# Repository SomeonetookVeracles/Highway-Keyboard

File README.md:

I'm building a minimalistic keyboard, something simple and stripped down. It's my first time working on a large PCB, and I kept getting distracted by feature creep and add-ons. So I'm going back to basics. I want this to be a barebones board that helps me sharpen my skills and really dial in the core of what makes a great keyboard.

I learned a lot while doing this, and explored concepts like impedence matching and zones, something that I've done before but never really had to prioritize.

If I do this again, I'm using a ESP-32 chip, making a CPU clock with decoupling capacitors was exhausting and annoyed me to no small extent lmao.

# Bill of Materials

| Reference | Qty | Value | Footprint | Description | DigiKey Link | Amazon Link | Unit Price | Total Price |
|-----------|-----|-------|-----------|-------------|--------------|-------------|------------|-------------|
| **Capacitors** | | | | | | | | |
| C1 | 1 | 1uF | 0603 | Ceramic Capacitor | [YAGEO CC0603ZRY5V7BB105](https://www.digikey.com/en/products/detail/yageo/CC0603ZRY5V7BB105/2103110) | [0603 Capacitor Kit](https://www.amazon.com/100pcs-Multilayer-Ceramic-Capacitor-0-5pF/dp/B0DDC637G1) | $0.03 | $0.03 |
| C2,C3,C4 | 3 | 0.1uF | 0603 | Ceramic Capacitor | [KEMET C0603C104J4RAC7867](https://www.digikey.com/en/products/detail/kemet/C0603C104J4RAC7867/411096) | [0603 Capacitor Kit](https://www.amazon.com/100pcs-Multilayer-Ceramic-Capacitor-0-5pF/dp/B0DDC637G1) | $0.02 | $0.06 |
| C5 | 1 | 10uF | 0603 | Ceramic Capacitor | [YAGEO CC0603KRX5R6BB106](https://www.digikey.com/en/products/detail/yageo/CC0603KRX5R6BB106/5195191) | [0603 Capacitor Kit](https://www.amazon.com/100pcs-Multilayer-Ceramic-Capacitor-0-5pF/dp/B0DDC637G1) | $0.08 | $0.08 |
| C6,C7 | 2 | 22pF | 0603 | Ceramic Capacitor | [DigiKey 0603 Capacitors](https://www.digikey.com/en/products/filter/ceramic-capacitors/60) | [0603 Capacitor Kit](https://www.amazon.com/100pcs-Multilayer-Ceramic-Capacitor-0-5pF/dp/B0DDC637G1) | $0.02 | $0.04 |
| **Diodes** | | | | | | | | |
| D1-D87 | 87 | D_Small | 0603 | Small Signal Diode | [DigiKey 0603 Diodes](https://www.digikey.com/en/products/filter/diodes-rectifiers-single/280) | [SMD Component Kit](https://www.amazon.com/Component-Assortment-Capacitor-Transistor-Soldering/dp/B07GMRJC1Q) | $0.05 | $4.35 |
| **Fuse** | | | | | | | | |
| F1 | 1 | 500mA | 1812 | PTC Resettable Fuse | [Bourns MF-MSMF050-2](https://www.digikey.com/en/products/detail/bourns-inc/MF-MSMF050-2/662832) | [Fuse Kit](https://www.amazon.com/s?k=500mA+PTC+fuse) | $0.32 | $0.32 |
| **Connectors** | | | | | | | | |
| J1 | 1 | USB_C_Receptacle | HRO TYPE-C-31-M-12 | USB-C 2.0 Connector | [JAE DX07S016JA3R1500](https://www.digikey.com/en/products/detail/jae-electronics/DX07S016JA3R1500/5978550) | [USB-C Connector](https://www.amazon.com/s?k=TYPE-C-31-M-12) | $0.38 | $0.38 |
| **Resistors** | | | | | | | | |
| R1,R4 | 2 | 10k | 0603 | Chip Resistor | [YAGEO RC0603JR-0710KL](https://www.digikey.com/en/products/detail/yageo/RC0603JR-0710KL/726700) | [0603 Resistor Kit](https://www.amazon.com/s?k=0603+resistor+kit) | $0.01 | $0.02 |
| R2,R3 | 2 | 22Ω | 0603 | Chip Resistor | [DigiKey 0603 Resistors](https://www.digikey.com/en/products/filter/resistors/chip-resistor-surface-mount/0603/52) | [0603 Resistor Kit](https://www.amazon.com/s?k=0603+resistor+kit) | $0.01 | $0.02 |
| R5 | 1 | 1M | 0603 | Chip Resistor | [DigiKey 0603 Resistors](https://www.digikey.com/en/products/filter/resistors/chip-resistor-surface-mount/0603/52) | [0603 Resistor Kit](https://www.amazon.com/s?k=0603+resistor+kit) | $0.01 | $0.01 |
| R6,R7 | 2 | 5.11k | 0603 | Chip Resistor | [DigiKey 0603 Resistors](https://www.digikey.com/en/products/filter/resistors/chip-resistor-surface-mount/0603/52) | [0603 Resistor Kit](https://www.amazon.com/s?k=0603+resistor+kit) | $0.01 | $0.02 |
| **Switches** | | | | | | | | |
| SW1-SW87 | 87 | SW_Push_45deg | Cherry MX Compatible | Mechanical Key Switch | [Cherry MX1A-E1NW](https://www.digikey.com/en/products/detail/cherry-americas-llc/MX1A-E1NW/20180) | [Cherry MX Switches](https://www.amazon.com/s?k=cherry+mx+switches) | $1.25 | $108.75 |
| SWRST1 | 1 | SW_PUSH | SMD Tactile | Reset Switch | [DigiKey Tactile Switches](https://www.digikey.com/en/products/filter/tactile-switches/197) | [Tactile Switch Kit](https://www.amazon.com/s?k=SMD+tactile+switch) | $0.15 | $0.15 |
| **Microcontroller** | | | | | | | | |
| U1 | 1 | ATmega32U4-A | TQFP-44 | 8-bit Microcontroller | [ATMEGA32U4-AU](https://www.digikey.com/en/products/detail/microchip-technology/ATMEGA32U4-AU/1914602) | [ATmega32U4 Module](https://www.amazon.com/s?k=atmega32u4) | $5.39 | $5.39 |
| **Crystal** | | | | | | | | |
| Y1 | 1 | 16MHz | 0603-4Pin | Crystal Oscillator | [TXC 7V-16.000MAAE-T](https://www.digikey.com/en/products/detail/txc-corporation/7V-16-000MAAE-T/2626978) | [16MHz Crystal](https://www.amazon.com/s?k=16MHz+crystal+SMD) | $0.35 | $0.35 |

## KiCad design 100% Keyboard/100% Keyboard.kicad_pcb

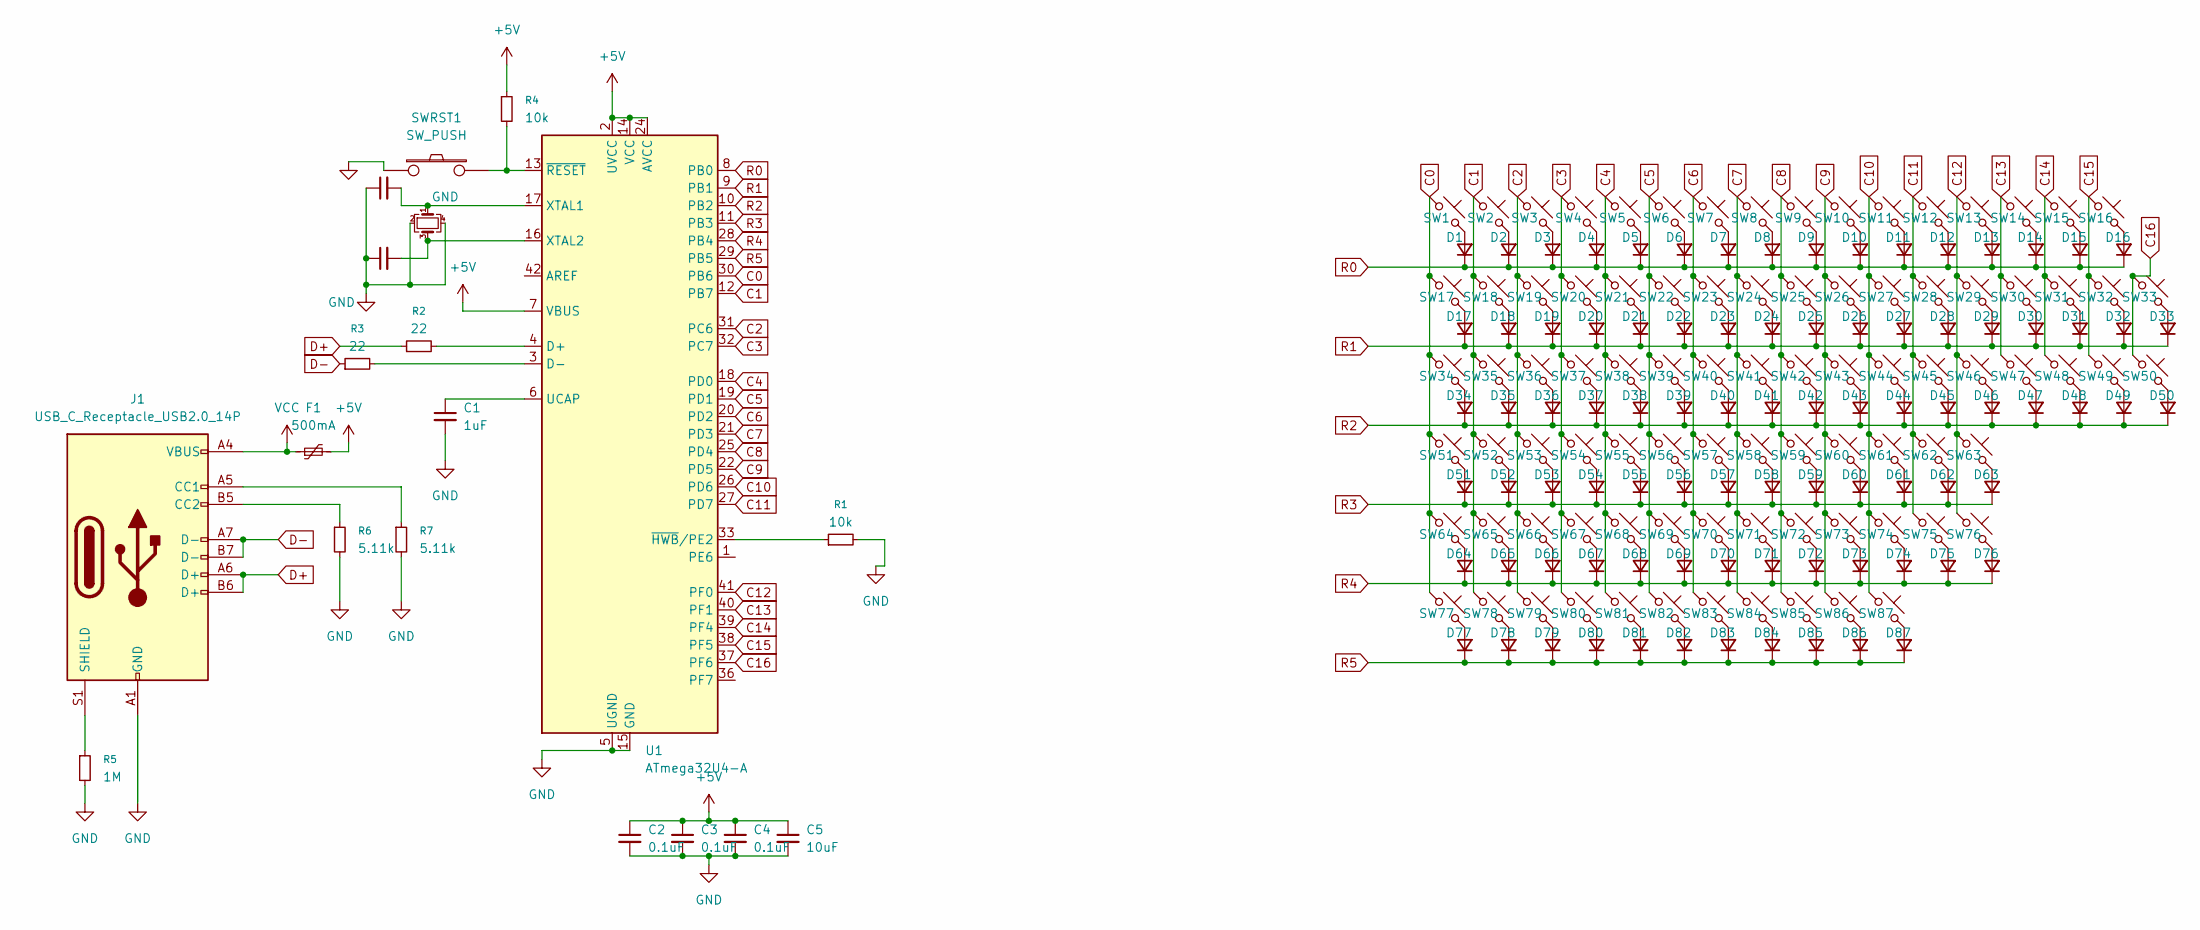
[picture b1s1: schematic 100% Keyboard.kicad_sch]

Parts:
C1: 1uF; C_0201_0603Metric_Pad0.64x0.40mm_HandSolder
C2, C3, C4: 0.1uF; C_0201_0603Metric_Pad0.64x0.40mm_HandSolder
C5: 10uF; C_0201_0603Metric_Pad0.64x0.40mm_HandSolder
C6, C7: 22pF; C_0201_0603Metric_Pad0.64x0.40mm_HandSolder
D1, D2, D3, D4, D5, D6, D7, D8, D9, D10, D11, D12, D13, D14, D15, D16, D17, D18, D19, D20, D21, D22, D23, D24, D25, D26, D27, D28, D29, D30, D31, D32, D33, D34, D35, D36, D37, D38, D39, D40, D41, D42, D43, D44, D45, D46, D47, D48, D49, D50, D51, D52, D53, D54, D55, D56, D57, D58, D59, D60, D61, D62, D63, D64, D65, D66, D67, D68, D69, D70, D71, D72, D73, D74, D75, D76, D77, D78, D79, D80, D81, D82, D83, D84, D85, D86, D87: D_Small; D_0603_1608Metric_Pad1.05x0.95mm_HandSolder
F1: 500mA; Fuse_Bourns_MF-RG500
J1: USB_C_Receptacle_USB2.0_14P; USB_C_Receptacle_HRO_TYPE-C-31-M-12
R1, R4: 10k; R_0201_0603Metric_Pad0.64x0.40mm_HandSolder
R2, R3: 22; R_0201_0603Metric_Pad0.64x0.40mm_HandSolder
R5: 1M; R_0201_0603Metric_Pad0.64x0.40mm_HandSolder
R6, R7: 5.11k; R_0201_0603Metric_Pad0.64x0.40mm_HandSolder
SW1, SW2, SW3, SW4, SW5, SW6, SW7, SW8, SW9, SW10, SW11, SW12, SW13, SW14, SW15, SW16, SW17, SW18, SW19, SW20, SW21, SW22, SW23, SW24, SW25, SW26, SW27, SW28, SW29, SW30, SW31, SW32, SW33, SW34, SW35, SW36, SW37, SW38, SW39, SW40, SW41, SW42, SW43, SW44, SW45, SW46, SW47, SW48, SW49, SW50, SW51, SW52, SW53, SW54, SW55, SW56, SW57, SW58, SW59, SW60, SW61, SW62, SW63, SW64, SW65, SW66, SW67, SW68, SW69, SW70, SW71, SW72, SW73, SW74, SW75, SW76, SW77, SW78, SW79, SW80, SW81, SW82, SW83, SW84, SW85, SW86, SW87: SW_Push_45deg; SW_Hybrid_Cherry_MX_Alps
SWRST1: SW_PUSH; SW_Push_1P1T_NO_CK_KMR2
U1: ATmega32U4-A; TQFP-44_10x10mm_P0.8mm
Y1: 16MHz; Crystal_SMD_0603-4Pin_6.0x3.5mm_HandSoldering

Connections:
+5V: C2.1, C3.1, C4.1, C5.1, F1.2, R4.1, U1.2 (UVCC), U1.7 (VBUS), U1.14 (VCC), U1.24 (AVCC), U1.34 (VCC), U1.44 (AVCC)
C0: SW1.1, SW17.1, SW34.1, SW51.1, SW64.1, SW77.1, U1.30 (PB6)
C1: SW2.1, SW18.1, SW35.1, SW52.1, SW65.1, SW78.1, U1.12 (PB7)
C2: SW3.1, SW19.1, SW36.1, SW53.1, SW66.1, SW79.1, U1.31 (PC6)
C3: SW4.1, SW20.1, SW37.1, SW54.1, SW67.1, SW80.1, U1.32 (PC7)
C4: SW5.1, SW21.1, SW38.1, SW55.1, SW68.1, SW81.1, U1.18 (PD0)
C5: SW6.1, SW22.1, SW39.1, SW56.1, SW69.1, SW82.1, U1.19 (PD1)
C6: SW7.1, SW23.1, SW40.1, SW57.1, SW70.1, SW83.1, U1.20 (PD2)
C7: SW8.1, SW24.1, SW41.1, SW58.1, SW71.1, SW84.1, U1.21 (PD3)
C8: SW9.1, SW25.1, SW42.1, SW59.1, SW72.1, SW85.1, U1.25 (PD4)
C9: SW10.1, SW26.1, SW43.1, SW60.1, SW73.1, SW86.1, U1.22 (PD5)
C10: SW11.1, SW27.1, SW44.1, SW61.1, SW74.1, SW87.1, U1.26 (PD6)
C11: SW12.1, SW28.1, SW45.1, SW62.1, SW75.1, U1.27 (PD7)
C12: SW13.1, SW29.1, SW46.1, SW63.1, SW76.1, U1.41 (PF0)
C13: SW14.1, SW30.1, SW47.1, U1.40 (PF1)
C14: SW15.1, SW31.1, SW48.1, U1.39 (PF4)
C15: SW16.1, SW32.1, SW49.1, U1.38 (PF5)
C16: SW33.1, SW50.1, U1.37 (PF6)
D+: J1.A6 (D+), J1.B6 (D+), R2.1
D-: J1.A7 (D-), J1.B7 (D-), R3.1
GND: C1.2, C2.2, C3.2, C4.2, C5.2, C6.1, C7.1, J1.A1 (GND), J1.A12 (GND), J1.B1 (GND), J1.B12 (GND), R1.2, R5.2, R6.2, R7.2, SWRST1.1, U1.5 (UGND), U1.15 (GND), U1.23 (GND), U1.35 (GND), U1.43 (GND), Y1.2, Y1.4
unnamed: D1.2 (A), SW1.2
unnamed: D2.2 (A), SW2.2
unnamed: D3.2 (A), SW3.2
unnamed: D4.2 (A), SW4.2
unnamed: D5.2 (A), SW5.2
unnamed: D6.2 (A), SW6.2
unnamed: D7.2 (A), SW7.2
unnamed: D8.2 (A), SW8.2
unnamed: D9.2 (A), SW9.2
unnamed: D10.2 (A), SW10.2
unnamed: D11.2 (A), SW11.2
unnamed: D12.2 (A), SW12.2
unnamed: D13.2 (A), SW13.2
unnamed: D14.2 (A), SW14.2
unnamed: D15.2 (A), SW15.2
unnamed: D16.2 (A), SW16.2
unnamed: D17.2 (A), SW17.2
unnamed: D18.2 (A), SW18.2
unnamed: D19.2 (A), SW19.2
unnamed: D20.2 (A), SW20.2
unnamed: D21.2 (A), SW21.2
unnamed: D22.2 (A), SW22.2
unnamed: D23.2 (A), SW23.2
unnamed: D24.2 (A), SW24.2
unnamed: D25.2 (A), SW25.2
unnamed: D26.2 (A), SW26.2
unnamed: D27.2 (A), SW27.2
unnamed: D28.2 (A), SW28.2
unnamed: D29.2 (A), SW29.2
unnamed: D30.2 (A), SW30.2
unnamed: D31.2 (A), SW31.2
unnamed: D32.2 (A), SW32.2
unnamed: D33.2 (A), SW33.2
unnamed: D34.2 (A), SW34.2
unnamed: D35.2 (A), SW35.2
unnamed: D36.2 (A), SW36.2
unnamed: D37.2 (A), SW37.2
unnamed: D38.2 (A), SW38.2
unnamed: D39.2 (A), SW39.2
unnamed: D40.2 (A), SW40.2
unnamed: D41.2 (A), SW41.2
unnamed: D42.2 (A), SW42.2
unnamed: D43.2 (A), SW43.2
unnamed: D44.2 (A), SW44.2
unnamed: D45.2 (A), SW45.2
unnamed: D46.2 (A), SW46.2
unnamed: D47.2 (A), SW47.2
unnamed: D48.2 (A), SW48.2
unnamed: D49.2 (A), SW49.2
unnamed: D50.2 (A), SW50.2
unnamed: D51.2 (A), SW51.2
unnamed: D52.2 (A), SW52.2
unnamed: D53.2 (A), SW53.2
unnamed: D54.2 (A), SW54.2
unnamed: D55.2 (A), SW55.2
unnamed: D56.2 (A), SW56.2
unnamed: D57.2 (A), SW57.2
unnamed: D58.2 (A), SW58.2
unnamed: D59.2 (A), SW59.2
unnamed: D60.2 (A), SW60.2
unnamed: D61.2 (A), SW61.2
unnamed: D62.2 (A), SW62.2
unnamed: D63.2 (A), SW63.2
unnamed: D64.2 (A), SW64.2
unnamed: D65.2 (A), SW65.2
unnamed: D66.2 (A), SW66.2
unnamed: D67.2 (A), SW67.2
unnamed: D68.2 (A), SW68.2
unnamed: D69.2 (A), SW69.2
unnamed: D70.2 (A), SW70.2
unnamed: D71.2 (A), SW71.2
unnamed: D72.2 (A), SW72.2
unnamed: D73.2 (A), SW73.2
unnamed: D74.2 (A), SW74.2
unnamed: D75.2 (A), SW75.2
unnamed: D76.2 (A), SW76.2
unnamed: D77.2 (A), SW77.2
unnamed: D78.2 (A), SW78.2
unnamed: D79.2 (A), SW79.2
unnamed: D80.2 (A), SW80.2
unnamed: D81.2 (A), SW81.2
unnamed: D82.2 (A), SW82.2
unnamed: D83.2 (A), SW83.2
unnamed: D84.2 (A), SW84.2
unnamed: D85.2 (A), SW85.2
unnamed: D86.2 (A), SW86.2
unnamed: D87.2 (A), SW87.2
unnamed: J1.A5 (CC1), R7.1
unnamed: J1.B5 (CC2), R6.1
unnamed: J1.S1 (SHIELD), R5.1
unnamed: R2.2, U1.4 (D+)
unnamed: R3.2, U1.3 (D-)
unnamed: C1.1, U1.6 (UCAP)
unnamed: C6.2, U1.17 (XTAL1), Y1.1
unnamed: C7.2, U1.16 (XTAL2), Y1.3
unnamed: R1.1, U1.33 (~HWB/PE2)
unnamed: R4.2, SWRST1.2, U1.13 (~RESET)
R0: D1.1 (K), D2.1 (K), D3.1 (K), D4.1 (K), D5.1 (K), D6.1 (K), D7.1 (K), D8.1 (K), D9.1 (K), D10.1 (K), D11.1 (K), D12.1 (K), D13.1 (K), D14.1 (K), D15.1 (K), D16.1 (K), U1.8 (PB0)
R1: D17.1 (K), D18.1 (K), D19.1 (K), D20.1 (K), D21.1 (K), D22.1 (K), D23.1 (K), D24.1 (K), D25.1 (K), D26.1 (K), D27.1 (K), D28.1 (K), D29.1 (K), D30.1 (K), D31.1 (K), D32.1 (K), D33.1 (K), U1.9 (PB1)
R2: D34.1 (K), D35.1 (K), D36.1 (K), D37.1 (K), D38.1 (K), D39.1 (K), D40.1 (K), D41.1 (K), D42.1 (K), D43.1 (K), D44.1 (K), D45.1 (K), D46.1 (K), D47.1 (K), D48.1 (K), D49.1 (K), D50.1 (K), U1.10 (PB2)
R3: D51.1 (K), D52.1 (K), D53.1 (K), D54.1 (K), D55.1 (K), D56.1 (K), D57.1 (K), D58.1 (K), D59.1 (K), D60.1 (K), D61.1 (K), D62.1 (K), D63.1 (K), U1.11 (PB3)
R4: D64.1 (K), D65.1 (K), D66.1 (K), D67.1 (K), D68.1 (K), D69.1 (K), D70.1 (K), D71.1 (K), D72.1 (K), D73.1 (K), D74.1 (K), D75.1 (K), D76.1 (K), U1.28 (PB4)
R5: D77.1 (K), D78.1 (K), D79.1 (K), D80.1 (K), D81.1 (K), D82.1 (K), D83.1 (K), D84.1 (K), D85.1 (K), D86.1 (K), D87.1 (K), U1.29 (PB5)
VCC: F1.1, J1.A4 (VBUS), J1.A9 (VBUS), J1.B4 (VBUS), J1.B9 (VBUS)

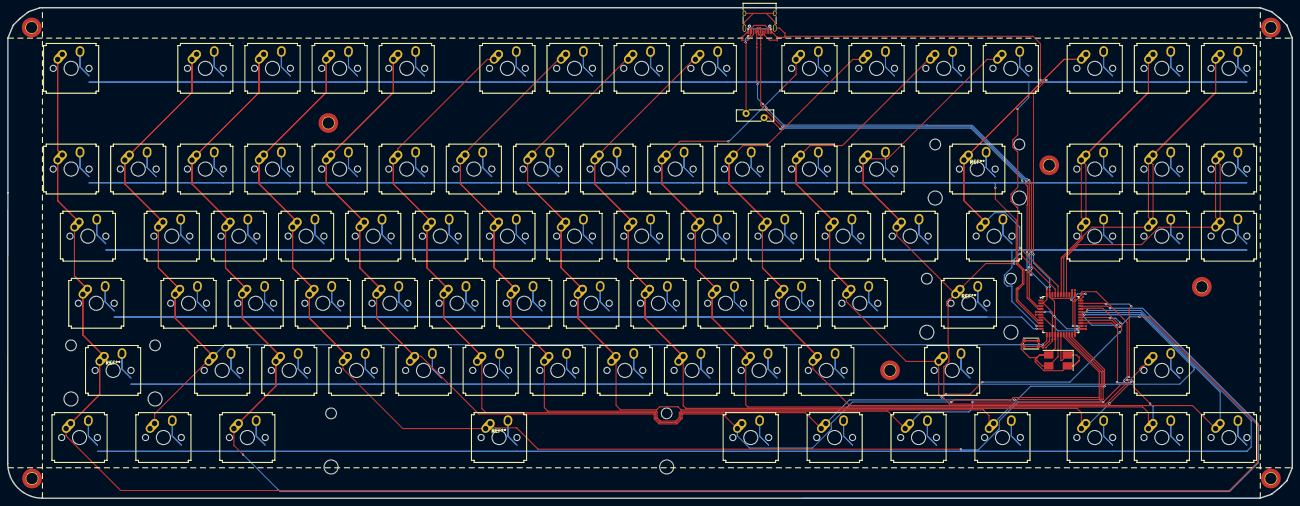
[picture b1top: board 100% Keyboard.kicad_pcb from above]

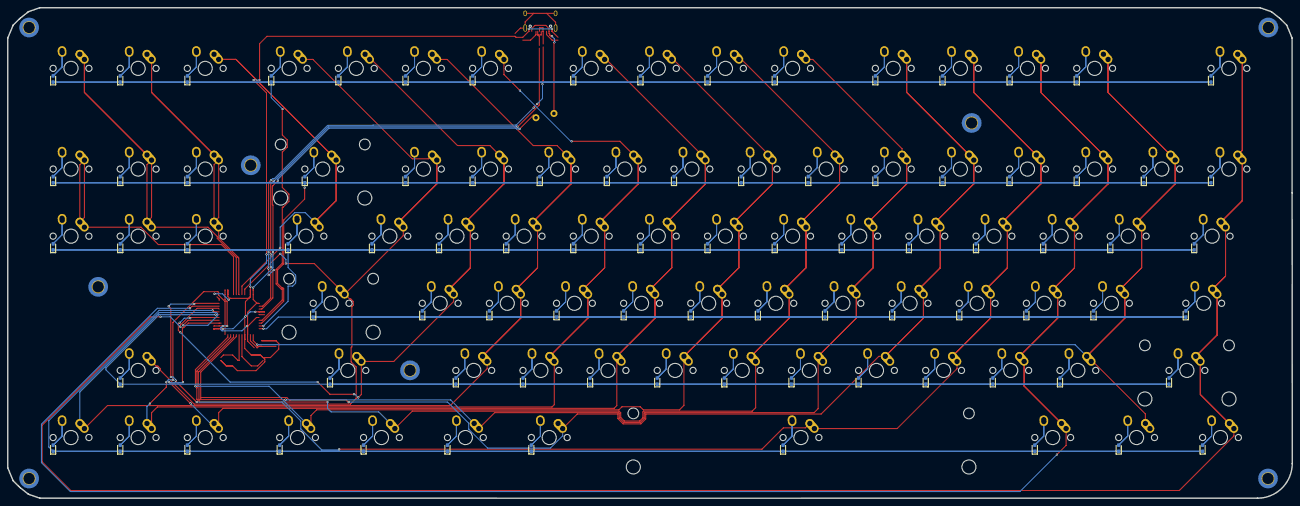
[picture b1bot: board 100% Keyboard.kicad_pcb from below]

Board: 2 copper layers, 364.6 x 139.2 mm, 193 parts (87 on the bottom side), 125 nets.

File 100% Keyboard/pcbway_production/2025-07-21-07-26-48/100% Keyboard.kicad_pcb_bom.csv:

Designator,Quantity,Value,Footprint,Package,MPN,DNP,Mount_Type,Description,Sim.Device,Sim.Pins
C1,1,1uF,C_0201_0603Metric_Pad0.64x0.40mm_HandSolder,,,,smt,"Unpolarized capacitor, small symbol",,
"C2, C3, C4",3,0.1uF,C_0201_0603Metric_Pad0.64x0.40mm_HandSolder,,,,smt,"Unpolarized capacitor, small symbol",,
C5,1,10uF,C_0201_0603Metric_Pad0.64x0.40mm_HandSolder,,,,smt,"Unpolarized capacitor, small symbol",,
"C6, C7",2,22pF,C_0201_0603Metric_Pad0.64x0.40mm_HandSolder,,,,smt,"Unpolarized capacitor, small symbol",,
"D1, D10, D11, D12, D13, D14, D15, D16, D17, D18, D19, D2, D20, D21, D22, D23, D24, D25, D26, D27, D28, D29, D3, D30, D31, D32, D33, D34, D35, D36, D37, D38, D39, D4, D40, D41, D42, D43, D44, D45, D46, D47, D48, D49, D5, D50, D51, D52, D53, D54, D55, D56, D57, D58, D59, D6, D60, D61, D62, D63, D64, D65, D66, D67, D68, D69, D7, D70, D71, D72, D73, D74, D75, D76, D77, D78, D79, D8, D80, D81, D82, D83, D84, D85, D86, D87, D9",87,D_Small,D_0603_1608Metric_Pad1.05x0.95mm_HandSolder,,,,smt,"Diode, small symbol",D,1=K 2=A
F1,1,500mA,Fuse_Bourns_MF-RG500,,,,tht,"Resettable fuse, polymeric positive temperature coefficient, small symbol",,
J1,1,USB_C_Receptacle_USB2.0_14P,USB_C_Receptacle_HRO_TYPE-C-31-M-12,,,,smt,USB 2.0-only 14P Type-C Receptacle connector,,
"R1, R4",2,10k,R_0201_0603Metric_Pad0.64x0.40mm_HandSolder,,,,smt,"Resistor, small symbol",,
"R2, R3",2,22,R_0201_0603Metric_Pad0.64x0.40mm_HandSolder,,,,smt,"Resistor, small symbol",,
R5,1,1M,R_0201_0603Metric_Pad0.64x0.40mm_HandSolder,,,,smt,"Resistor, small symbol",,
"R6, R7",2,5.11k,R_0201_0603Metric_Pad0.64x0.40mm_HandSolder,,,,smt,"Resistor, small symbol",,
"SW1, SW10, SW11, SW12, SW13, SW14, SW15, SW16, SW17, SW18, SW19, SW2, SW20, SW21, SW22, SW23, SW24, SW25, SW26, SW27, SW28, SW29, SW3, SW30, SW31, SW32, SW33, SW34, SW35, SW36, SW37, SW38, SW39, SW4, SW40, SW41, SW42, SW43, SW44, SW45, SW46, SW47, SW48, SW49, SW5, SW50, SW51, SW52, SW53, SW54, SW55, SW56, SW57, SW58, SW59, SW6, SW60, SW61, SW62, SW63, SW64, SW65, SW66, SW67, SW68, SW69, SW7, SW70, SW71, SW72, SW73, SW74, SW75, SW76, SW77, SW78, SW79, SW8, SW80, SW81, SW82, SW83, SW84, SW85, SW86, SW87, SW9",87,SW_Push_45deg,SW_Hybrid_Cherry_MX_Alps,,,,tht,"Push button switch, normally open, two pins, 45° tilted",,
SWRST1,1,SW_PUSH,SW_Push_1P1T_NO_CK_KMR2,,,,smt,,,
U1,1,ATmega32U4-A,TQFP-44_10x10mm_P0.8mm,,,,smt,"16MHz, 32kB Flash, 2.5kB SRAM, 1kB EEPROM, USB 2.0, TQFP-44",,
Y1,1,16MHz,Crystal_SMD_0603-4Pin_6.0x3.5mm_HandSoldering,,,,smt,"Four pin crystal, GND on pins 2 and 4, small symbol",,

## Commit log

2025-06-23 First push (i forgor)
2025-07-22 Kill me
2025-07-27 Added BOM
2025-08-02 Fixes!
